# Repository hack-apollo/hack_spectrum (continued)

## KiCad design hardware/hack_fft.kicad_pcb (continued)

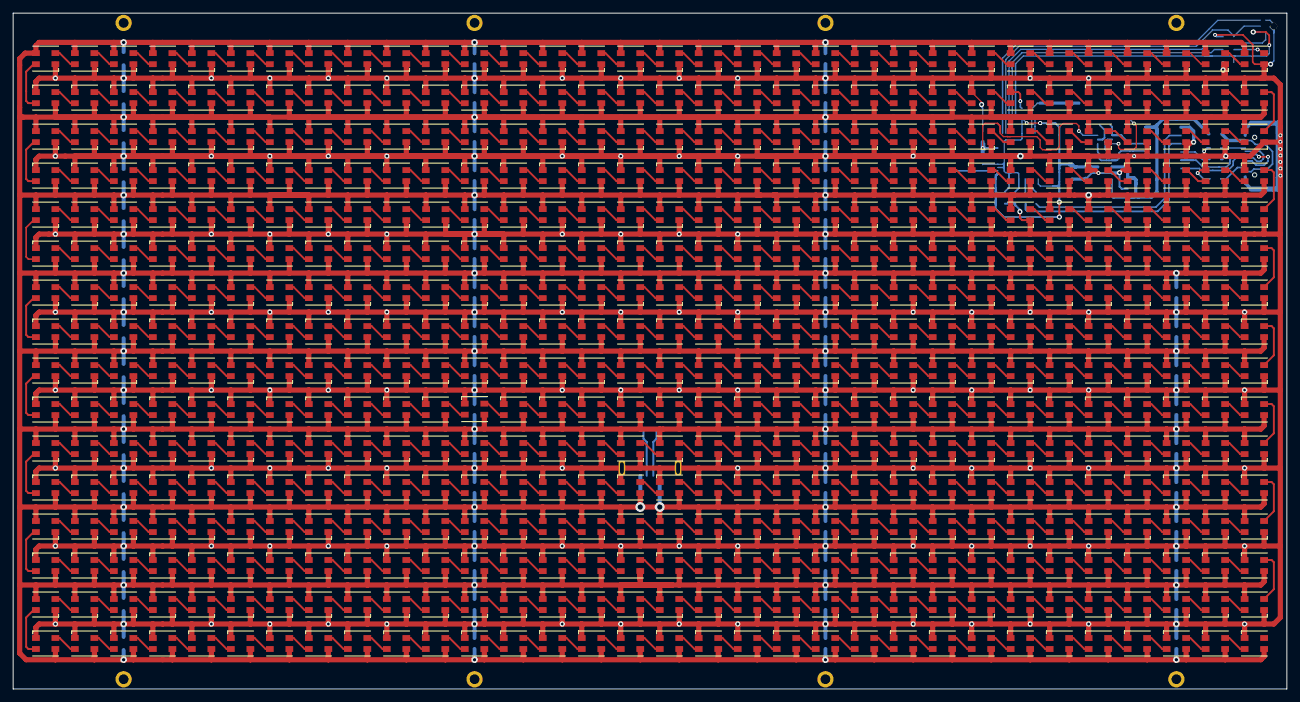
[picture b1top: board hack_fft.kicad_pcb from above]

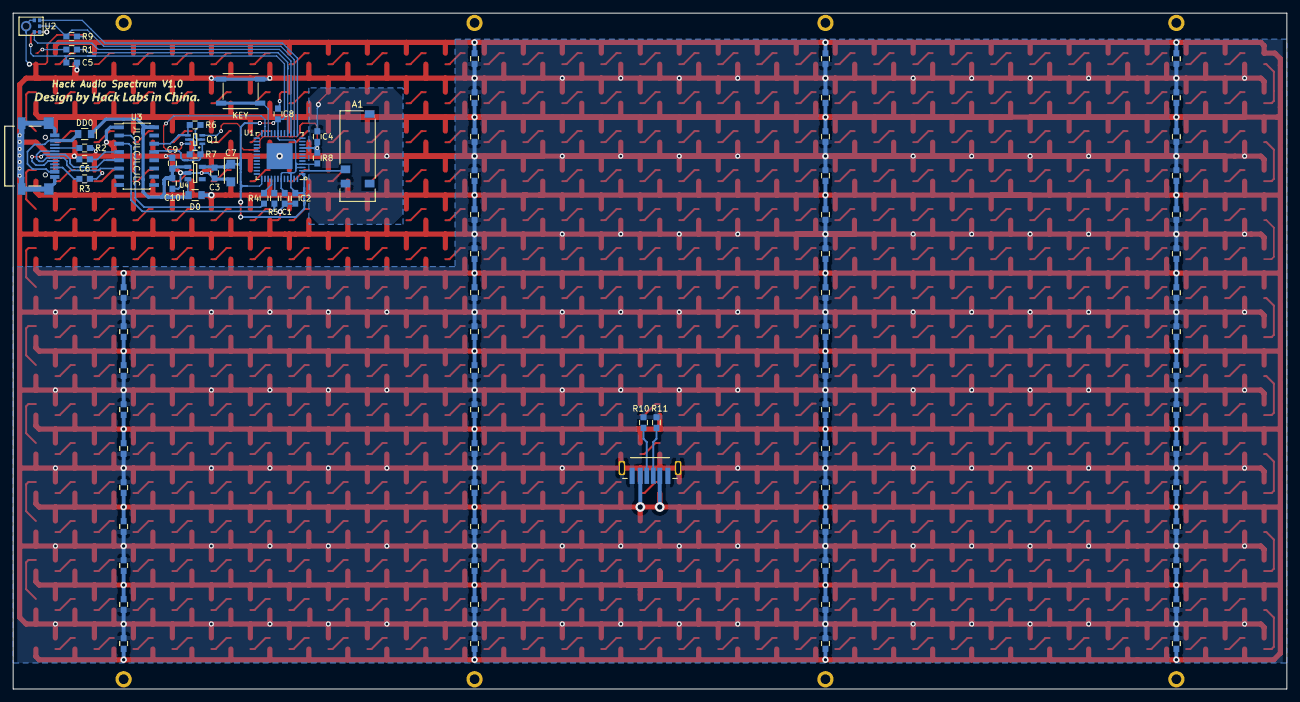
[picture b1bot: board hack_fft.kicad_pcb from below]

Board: 2 copper layers, 196.0 x 104.0 mm, 610 parts (90 on the bottom side), 540 nets.

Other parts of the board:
De: WS2812B; LED_WS2812B_3.5x3.5mm
P6, P6#2, P6#3, P6#4, P6#5, P6#6, P6#7, P6#8: CON_1; CON1

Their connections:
/V_RGB: De.1; also elsewhere on the board
GND: De.3; also elsewhere on the board
unnamed 58: De.4; also elsewhere on the board
unnamed 59: De.2; also elsewhere on the board

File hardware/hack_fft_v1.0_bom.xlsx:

编号 | 名称 | 值 | 封装 | 数量 | 备注
R1,R4,R5 |  | 100Ω | 0603_R | 3
R2,R3,R10,R11 |  | 5.1KΩ | 0603_R | 4
R6,R7,R8 |  | 10KΩ | 0603_R | 3
R9 |  | 100KΩ | 0603_R | 1
C1,C2,C3,C4,C8,C10,C101&C410 | X5R | 1uF/50V | 0603_C | 64
C5,C6,C9 | X7R | 0.1uF/50V | 0603_C | 3
C7 | 钽电容 | 10uF/16V | A型 3216 | 1
D1~D512 | WS2812B-3535 |  |  | 512
D0,DD0 | 肖特基二极管 | 1N5819WS | SOD-323 | 2
Q1 | BC847BS |  | SOT-363 | 1
U1 | ESP32-PICO-D4 |  | QFN-48 | 1
U2 | ICS-43434 |  | LGA-CAV-6 | 1
U3 | CH340C |  | SOP-16 | 1
U4 | SPX3819M5-L-3-3 |  | SOT23-5 | 1
A1 | PRO-OB-440 | 2.4G射频天线
SW1 | 轻触开关 | 高8mm | 4*4*8MM | 1 | 关键字“4*4*8MM”
P1 | USB-Type-C母座 | SMT全贴片式 16P |  | 1 | 关键字“USB3.1 Type-C 母座 SMT全贴片式 16P”
P2 | USB-Type-C母座 | Type-C 6P 立式贴片6.8mm |  | 1 | 关键字“Type-C母座6P 立式贴片6.8mm”
P6 x8 | 圆头自攻螺丝十字 | M1.4*6 |  | 8
如果整理有误还望见谅，可到“HACK实验室”微信公众号私信通知修改，谢谢！

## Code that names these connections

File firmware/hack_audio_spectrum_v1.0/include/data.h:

/*********************************************************************************************************
  HackLabs_Audio_Spectrum                                                                               
  ********************************************************************************************************
  Author: HACK实验室                                                                                     
  YouTubeID: HACK实验室, welcome to subscribe：https://www.youtube.com/channel/UCxFY1FcIYK9d7riTvIh6eiA                                                          
  Version 1.0 
  Hack_Audio_Spectrum is a free download and may be used, modified, evaluated and
  distributed without charge provided the user adheres to version hree of the GNU
  General Public License (GPL) and does not remove the copyright notice or this
  text. The GPL V3 text is available on the gnu.org web site

  作者：HACK实验室                                                                                        
  B站ID：HACK实验室  欢迎订阅：https://space.bilibili.com/395145107                                                                             
  微信公众号：HACK实验室，开源资料唯一发布点，定期分享开源硬件以及有价值的技术文章，欢迎关注.                        
  Version 1.0                                                                                           
  Hack_Audio_Spectrum 是一个完全开源的硬件项目，允许用户免费下载使用，但需遵守GPL V3开源协议，协议文本可在开源文件根目录或gnu.org网站上获得.  
*********************************************************************************************************/

#include <arduinoFFT.h>
#include <driver/i2s.h>


#define I2S_WS    33
#define I2S_SD    25
#define I2S_SCK   26

const i2s_port_t I2S_PORT = I2S_NUM_0;
const int SAMPLE_BLOCK = 64;
const int SAMPLE_FREQ = 10240;

int gain=40;  //adjust it to set the gain   
uint16_t audio_data;                            

const uint16_t samples = 512;
unsigned int sampling_period_us;
unsigned long microseconds;

double vReal[samples];
double vImag[samples];
double fft_bin[samples];

double fft_data[32];
int fft_result[32]; 

//adjust single frequency curves.
double fft_freq_boost[32] = {1.02,1.03,1.04,1.06,1.08,1.10,1.10,1.11,1.12,1.13,1.15,1.16,1.17,1.18,1.20,1.21,1.30,1.51,2.11,2.22,3.25,3.26,3.52,3.55,4.22,4.24,5.52,5.55,6.53,6.55,8.82,8.88};

TaskHandle_t fft_task;

arduinoFFT FFT = arduinoFFT( vReal, vImag, samples, SAMPLE_FREQ);

double fft_add( int from, int to) {
  int i = from;
  double result = 0;
  while ( i <= to) {
    result += fft_bin[i++];
  }
  return result;
}

void fft_code( void * parameter) {

  for(;;) {

    delay(1);          

    microseconds = micros();

    for(int i=0; i<samples; i++) {
      int32_t digitalSample = 0;
      int bytes_read = i2s_pop_sample(I2S_PORT, (char *)&digitalSample, portMAX_DELAY); // no timeout
      if (bytes_read > 0) {
        audio_data = abs(digitalSample >> 16);
      }
      vReal[i] = audio_data; 
      vImag[i] = 0;
      microseconds += sampling_period_us;
    }

    FFT.Windowing( FFT_WIN_TYP_HAMMING, FFT_FORWARD ); 
    FFT.Compute( FFT_FORWARD ); 
    FFT.ComplexToMagnitude(); 

    for (int i = 0; i < samples; i++) {   
      double t = 0.0;
      t = abs(vReal[i]);
      t = t / 16.0;    
      fft_bin[i] = t;
    }

    fft_data[0]  = (fft_add(3,4))/2;       // 60-100Hz
    fft_data[1]  = (fft_add(4,5))/2;       // 80-120Hz
    fft_data[2]  = (fft_add(5,6))/2;       // 100-140Hz
    fft_data[3]  = (fft_add(6,7))/2;       // 120-160Hz
    fft_data[4]  = (fft_add(7,8))/2;       // 140-180Hz
    fft_data[5]  = (fft_add(8,9))/2;       // 160-200Hz
    fft_data[6]  = (fft_add(9,10))/2;      // 180-220Hz
    fft_data[7]  = (fft_add(10,11))/2;     // 200-240Hz
    fft_data[8]  = (fft_add(11,12))/2;     // 220-260Hz
    fft_data[9]  = (fft_add(12,13))/2;     // 240-280Hz
    fft_data[10] = (fft_add(13,14))/2;     // 260-300Hz
    fft_data[11] = (fft_add(14,16))/3;     // 280-340Hz
    fft_data[12] = (fft_add(16,18))/3;     // 320-380Hz
    fft_data[13] = (fft_add(18,20))/3;     // 360-420Hz
    fft_data[14] = (fft_add(20,24))/5;     // 400-500Hz
    fft_data[15] = (fft_add(24,28))/5;     // 480-580Hz
    fft_data[16] = (fft_add(28,32))/5;     // 560-660Hz
    fft_data[17] = (fft_add(32,36))/5;     // 640-740Hz
    fft_data[18] = (fft_add(36,42))/7;     // 720-860Hz
    fft_data[19] = (fft_add(42,48))/7;     // 840-980Hz
    fft_data[20] = (fft_add(48,56))/9;     // 960-1140Hz
    fft_data[21] = (fft_add(56,64))/9;     // 1120-1300Hz
    fft_data[22] = (fft_add(64,74))/11;    // 1280-1500Hz
    fft_data[23] = (fft_add(74,84))/11;    // 1480-1700Hz
    fft_data[24] = (fft_add(84,97))/14;    // 1680-1960Hz
    fft_data[25] = (fft_add(97,110))/14;   // 1940-2240Hz
    fft_data[26] = (fft_add(110,128))/19;  // 2200-2580Hz
    fft_data[27] = (fft_add(128,146))/19;  // 2560-2940Hz
    fft_data[28] = (fft_add(146,170))/25;  // 2920-3420Hz
    fft_data[29] = (fft_add(170,194))/25;  // 3400-3900Hz
    fft_data[30] = (fft_add(194,224))/31;  // 3880-4500Hz
    fft_data[31] = (fft_add(224,255))/32;  // 4520-5120Hz

    //adjust single frequency curves.
    for (int i=0; i < 32; i++) {
      fft_data[i] = fft_data[i] * fft_freq_boost[i];
    }

    //adjust overall frequency curves.
    for (int i=0; i < 32; i++) {
      fft_data[i] = fft_data[i] * gain / 50;
    }

    //constraint function
    for (int i=0; i < 32; i++) {
      fft_result[i] = constrain((int)fft_data[i],0,255);
    }
  }
}

void audio_receive() {
    
  esp_err_t err;
  const i2s_config_t i2s_config = {
    .mode = i2s_mode_t(I2S_MODE_MASTER | I2S_MODE_RX), 
    .sample_rate = SAMPLE_FREQ * 2,                       // 10240*2=20480Hz
    .bits_per_sample = I2S_BITS_PER_SAMPLE_32BIT, 
    .channel_format = I2S_CHANNEL_FMT_ONLY_LEFT,  
    .communication_format = i2s_comm_format_t(I2S_COMM_FORMAT_I2S | I2S_COMM_FORMAT_I2S_MSB),
    .intr_alloc_flags = ESP_INTR_FLAG_LEVEL1,
    .dma_buf_count = 8, 
    .dma_buf_len = SAMPLE_BLOCK
  };

  const i2s_pin_config_t pin_config = {
    .bck_io_num = I2S_SCK,
    .ws_io_num = I2S_WS,
    .data_out_num = -1, 
    .data_in_num = I2S_SD 
  };
  
  err = i2s_driver_install(I2S_PORT, &i2s_config, 0, NULL);
  if (err != ESP_OK) {
    Serial.printf("Failed installing driver: %d\n", err);
    while (true);
  }
  err = i2s_set_pin(I2S_PORT, &pin_config);
  if (err != ESP_OK) {
    Serial.printf("Failed setting pin: %d\n", err);
    while (true);
  }
  Serial.println("I2S driver installed.");
  delay(100);
  
  sampling_period_us = round(1000000*(1.0/SAMPLE_FREQ));
  
  xTaskCreatePinnedToCore(
        fft_code,                    //Task function
        "FFT",                       //Task name
        10000,                       //Task stack size(units:byte)
        NULL,                        //Parameters passed to the task function
        1,                           //Task priority
        &fft_task,                   //Task handle
        0);                          //Specifies the core to run the task
}

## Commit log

2022-03-14 first add
2022-03-14 Create LICENSE
2022-04-29 exact espressif32 version @3.5.0
2022-08-24 修复最上一行不显示的错误
    修复最上一行不显示的错误。
